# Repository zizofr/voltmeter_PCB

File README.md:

# ⚡ Digital Voltmeter (Custom PCB & Hardware Design)

A compact digital voltmeter designed around a custom Printed Circuit Board (PCB) created in KiCad. This repository contains the complete hardware design files, schematics, Gerber manufacturing outputs, and board renders prior to final firmware integration.

---

## 🖼️ Hardware & PCB Gallery

### Board Renders & Views
| Top View | Bottom View |
| :---: | :---: |
|  |  |

| Perspective View 1 | Perspective View 2 |
| :---: | :---: |
|  |  |

---

## 🛠️ Project Specifications & Features

- **EDA Tool:** KiCad
- **Board Architecture:** Custom 2-layer PCB
- **Hardware Features:**
  - Dedicated analog front-end voltage divider circuit for signal attenuation.
  - Onboard microcontroller interface for ADC sampling and processing.
  - Display interface output.
  - Optimized trace routing with solid ground plane shielding.
- **Manufacturing Package:** Full Gerber layer generation (F_Cu, B_Cu, Solder Masks, Silkscreens, and Drill files).

---

## 📂 Repository Structure

```text
├── gerber/              # Production Gerber and drill files (.gbr, .drl)
├── view_1.png              # High-resolution 3D renders (top, bottom, view_1, view_2)
├──view_2.png
├──top.png
├──bottom.png
├──firmware.ino  # ATmega328P C++ source code
├── voltmeter.kicad_pcb  # KiCad PCB board layout source file
├── voltmeter.kicad_sch  # KiCad schematic design source file
└── README.md            # Project documentation

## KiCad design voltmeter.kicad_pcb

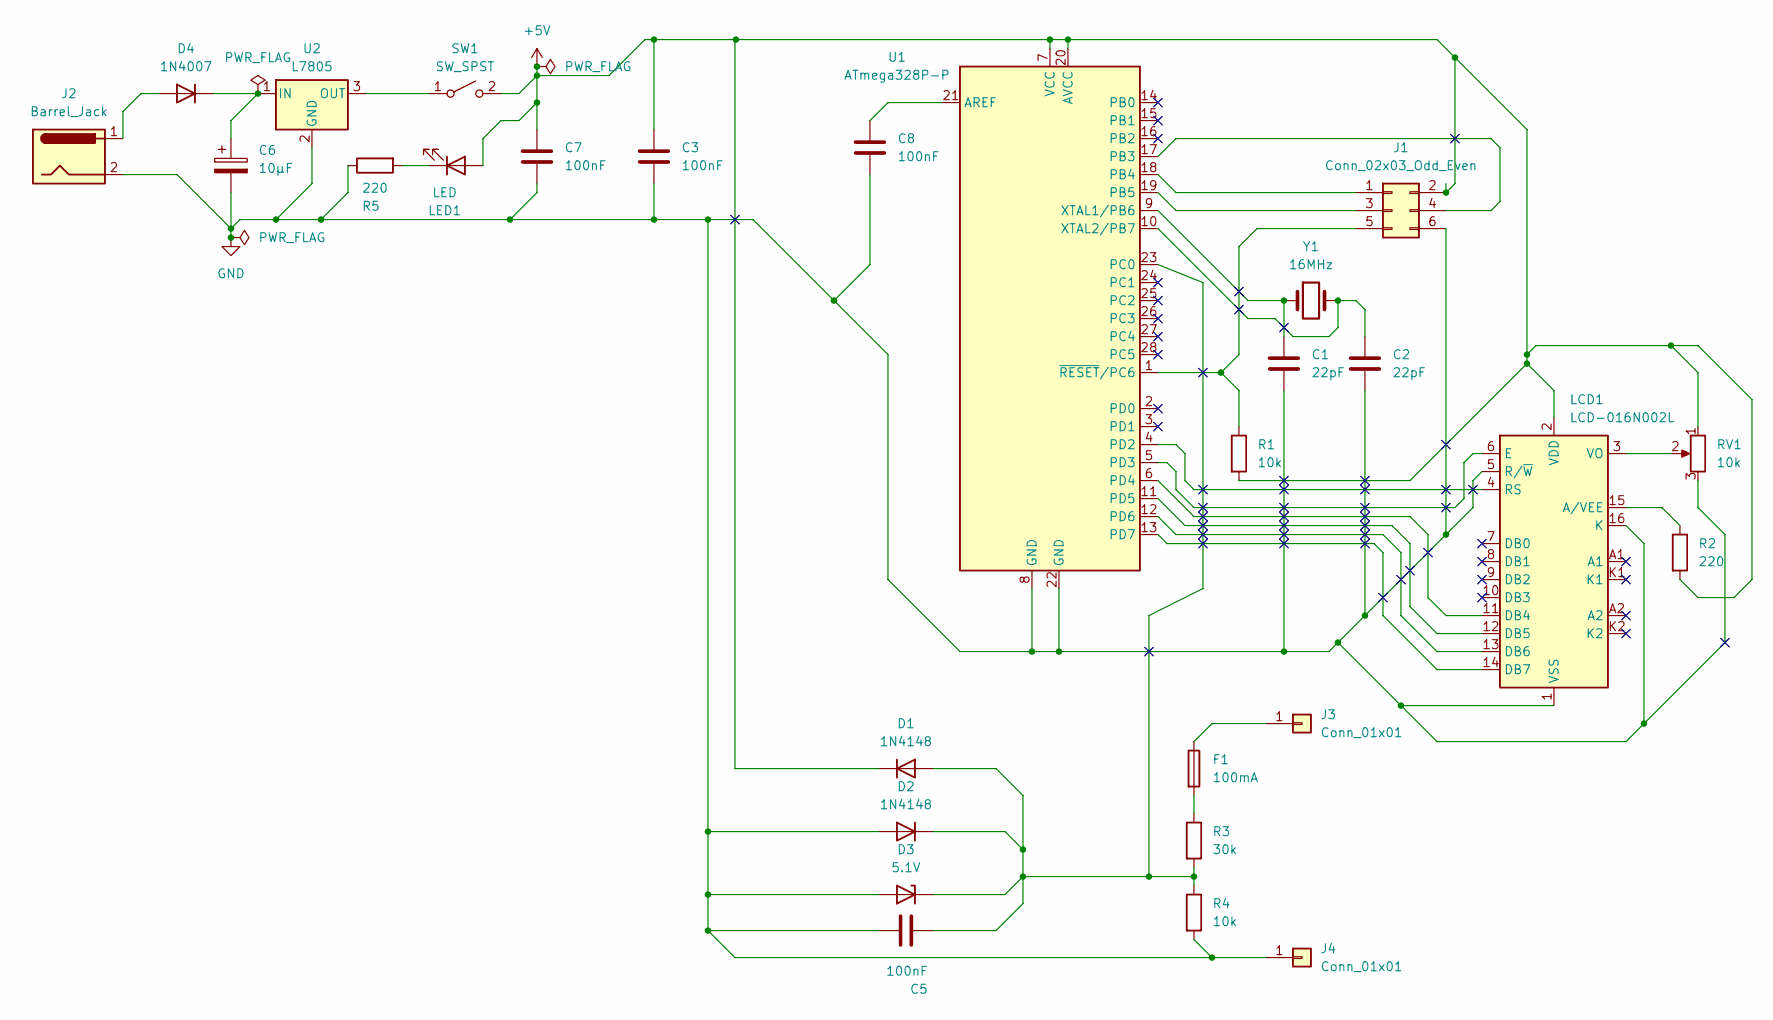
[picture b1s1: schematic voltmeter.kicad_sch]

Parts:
C1, C2: 22pF; C_Disc_D5.0mm_W2.5mm_P5.00mm
C3, C5, C7, C8: 100nF; C_Disc_D5.0mm_W2.5mm_P5.00mm
C6: 10µF; CP_Radial_D5.0mm_P2.00mm
D1, D2: 1N4148; D_DO-35_SOD27_P7.62mm_Horizontal
D3: 5.1V; D_DO-35_SOD27_P7.62mm_Horizontal
D4: 1N4007; D_DO-41_SOD81_P10.16mm_Horizontal
F1: 100mA; Fuse_1206_3216Metric
J1: Conn_02x03_Odd_Even; PinHeader_2x03_P2.54mm_Vertical
J2: Barrel_Jack; BarrelJack_Horizontal
J3, J4: Conn_01x01; Banana_Jack_1Pin
LCD1: LCD-016N002L; PinHeader_1x16_P2.54mm_Vertical
LED1: LED; LED_D5.0mm
R1, R4: 10k; R_Axial_DIN0207_L6.3mm_D2.5mm_P10.16mm_Horizontal
R2, R5: 220; R_Axial_DIN0207_L6.3mm_D2.5mm_P10.16mm_Horizontal
R3: 30k; R_Axial_DIN0207_L6.3mm_D2.5mm_P10.16mm_Horizontal
RV1: 10k; Potentiometer_Bourns_3386P_Vertical
SW1: SW_SPST; SW_SPST_Omron_B3F-40xx
U1: ATmega328P-P; DIP-28_W7.62mm
U2: L7805; TO-220-3_Vertical
Y1: 16MHz; Crystal_HC49-4H_Vertical

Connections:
+5V: C3.1, C7.1, D1.1 (K), J1.2, LCD1.2 (VDD), LED1.2 (A), R1.2, R2.2, RV1.1, SW1.2 (B), U1.7 (VCC), U1.20 (AVCC)
GND: C1.2, C2.2, C3.2, C5.2, C6.2, C7.2, C8.2, D2.2 (A), D3.2 (A), J1.6, J2.2, J4.1 (Pin_1_1), LCD1.1 (VSS), LCD1.5 (R/~W), LCD1.16 (K), R4.2, R5.1, RV1.3, U1.8 (GND), U1.22 (GND), U2.2 (GND)
unnamed: C5.1, D1.2 (A), D2.1 (K), D3.1 (K), R3.2, R4.1, U1.23 (PC0)
unnamed: D4.2 (A), J2.1
unnamed: C6.1, D4.1 (K), U2.1 (IN)
unnamed: F1.2, R3.1
unnamed: J1.1, U1.18 (PB4)
unnamed: J1.3, U1.19 (PB5)
unnamed: J1.4, U1.17 (PB3)
unnamed: J1.5, R1.1, U1.1 (~RESET/PC6)
unnamed: F1.1, J3.1 (Pin_1_1)
unnamed: LCD1.15 (A/VEE), R2.1
unnamed: LCD1.11 (DB4), U1.6 (PD4)
unnamed: LCD1.12 (DB5), U1.11 (PD5)
unnamed: LCD1.13 (DB6), U1.12 (PD6)
unnamed: LCD1.14 (DB7), U1.13 (PD7)
unnamed: LCD1.6 (E), U1.5 (PD3)
unnamed: LCD1.4 (RS), U1.4 (PD2)
unnamed: LCD1.3 (VO), RV1.2
unnamed: LED1.1 (K), R5.2
unnamed: SW1.1 (A), U2.3 (OUT)
unnamed: C8.1, U1.21 (AREF)
unnamed: C1.1, U1.9 (XTAL1/PB6), Y1.1
unnamed: C2.1, U1.10 (XTAL2/PB7), Y1.2

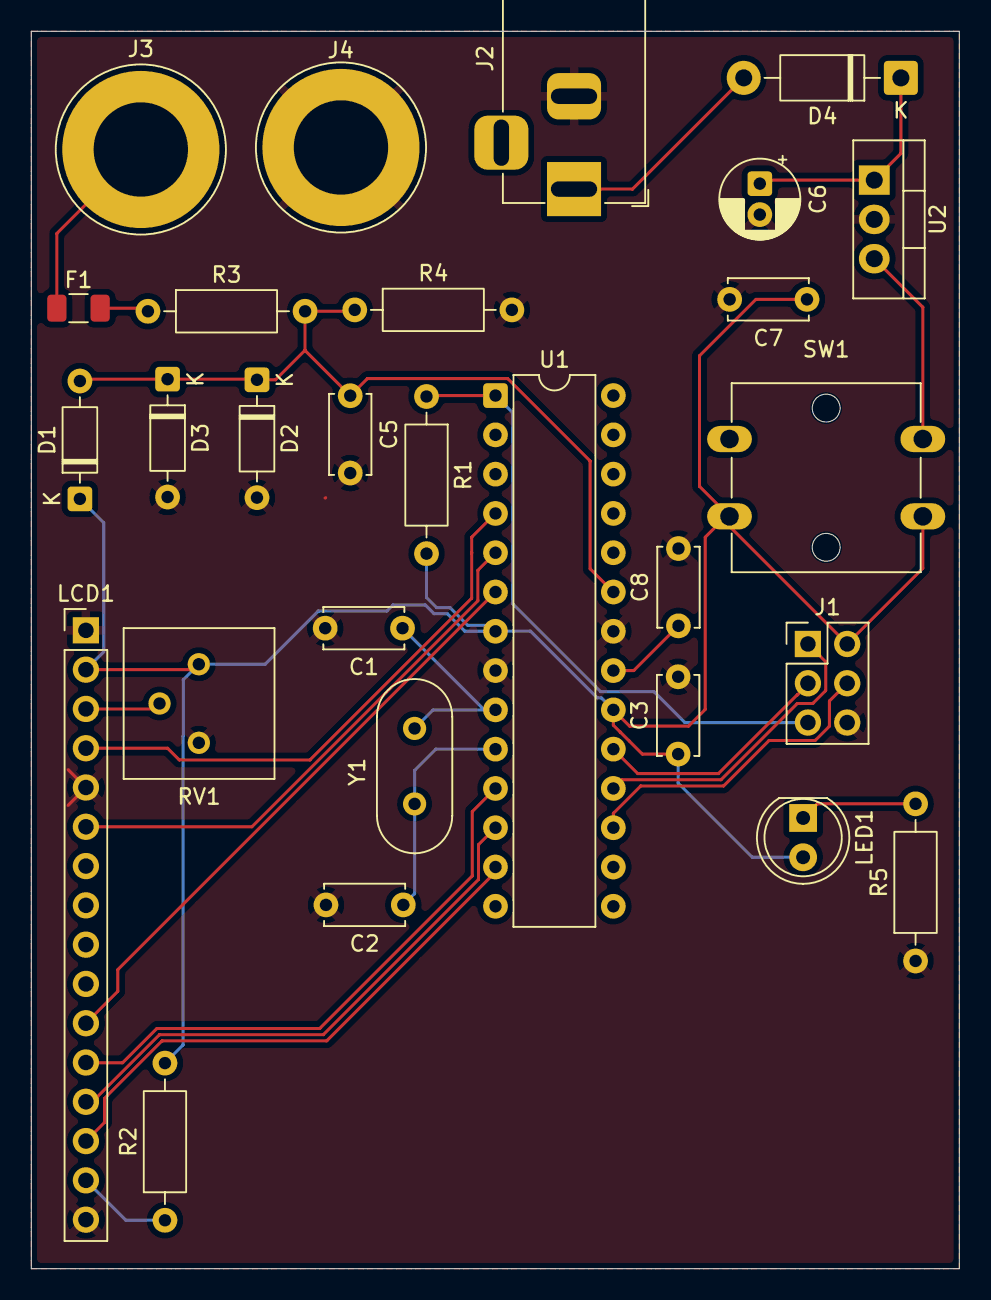
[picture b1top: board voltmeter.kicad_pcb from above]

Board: 2 copper layers, 60.0 x 80.0 mm, 28 parts (0 on the bottom side), 24 nets.

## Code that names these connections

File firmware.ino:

/*
  ============================================
  Digital Voltmeter - Official Firmware v1.0
  ============================================

  Target chip: ATmega328P-P (bare chip, 16MHz external crystal,
  programmed via ISP through J1)

  Function: Reads a 0-20V DC input through a resistor divider
  on ADC0, and displays the measured voltage on a 16x2 LCD.

  --------------------------------------------
  HARDWARE PIN MAPPING (matches the schematic)
  --------------------------------------------
  ATmega pin | Arduino name | Function
  -----------|--------------|------------------
  Pin 4      | D2 (PD2)     | LCD RS
  Pin 5      | D3 (PD3)     | LCD E
  Pin 6      | D4 (PD4)     | LCD DB4
  Pin 11     | D5 (PD5)     | LCD DB5
  Pin 12     | D6 (PD6)     | LCD DB6
  Pin 13     | D7 (PD7)     | LCD DB7
  Pin 23     | A0 (PC0)     | ADC input (from R3/R4 divider)

  --------------------------------------------
  VOLTAGE DIVIDER
  --------------------------------------------
  R3 = 30k (top, from probe input)
  R4 = 10k (bottom, to GND)
  Scales 0-20V input down to 0-5V at the ADC pin.
  Ratio to undo in software = (R3+R4)/R4 = 4.0

  --------------------------------------------
  BEFORE FIRST REAL USE
  --------------------------------------------
  1. Burn the bootloader onto U1 via J1 (if not already done),
     using an Arduino-as-ISP or USBasp programmer, board setting
     "Arduino Uno" (same chip/fuses/16MHz crystal).
  2. Upload this sketch through the same ISP connection.
  3. Calibrate: apply a known, accurate voltage (measured with a
     trusted multimeter) to the probes, and adjust
     CALIBRATION_FACTOR below until the LCD matches that reading.
     Re-upload after changing it.
*/

#include <LiquidCrystal.h>

// ---------------- Pin setup ----------------
const int PIN_RS = 2;
const int PIN_EN = 3;
const int PIN_D4 = 4;
const int PIN_D5 = 5;
const int PIN_D6 = 6;
const int PIN_D7 = 7;

LiquidCrystal lcd(PIN_RS, PIN_EN, PIN_D4, PIN_D5, PIN_D6, PIN_D7);

const int ADC_PIN = A0;

// ---------------- Circuit constants ----------------
const float VREF = 5.0;             // ADC reference voltage (AVCC/AREF)
const int   ADC_MAX = 1023;         // 10-bit ADC resolution
const float DIVIDER_RATIO = 4.0;    // (R3 + R4) / R4 = (30k + 10k) / 10k

// ---------------- Calibration ----------------
// Set this after testing against a known-accurate voltage source.
// Formula: CALIBRATION_FACTOR = actual / displayed
float CALIBRATION_FACTOR = 1.0;

// ---------------- Sampling ----------------
const int   NUM_SAMPLES     = 30;   // averaged per reading, reduces noise/jitter
const int   SAMPLE_DELAY_MS = 2;    // small delay between samples
const int   UPDATE_DELAY_MS = 250;  // how often the display refreshes

// ---------------- Safety display ----------------
const float OVER_RANGE_VOLTS = 20.5; // slightly above rated 20V max

void setup() {
  lcd.begin(16, 2);
  lcd.clear();
  lcd.setCursor(0, 0);
  lcd.print("Digital");
  lcd.setCursor(0, 1);
  lcd.print("Voltmeter v1.0");
  delay(1500);
  lcd.clear();
}

void loop() {
  float vIn = readVoltage();

  lcd.setCursor(0, 0);
  lcd.print("Voltage:");

  lcd.setCursor(0, 1);
  if (vIn > OVER_RANGE_VOLTS) {
    lcd.print("OVER RANGE!   ");
  } else {
    lcd.print(vIn, 2);
    lcd.print(" V");
    lcd.print("      "); // clears leftover digits from a previous longer reading
  }

  delay(UPDATE_DELAY_MS);
}

// Reads and averages the ADC, then converts to the real input voltage
float readVoltage() {
  long sum = 0;
  for (int i = 0; i < NUM_SAMPLES; i++) {
    sum += analogRead(ADC_PIN);
    delay(SAMPLE_DELAY_MS);
  }
  float rawAverage = sum / (float)NUM_SAMPLES;

  float vAtPin = (rawAverage / (float)ADC_MAX) * VREF;
  float vIn = vAtPin * DIVIDER_RATIO * CALIBRATION_FACTOR;

  return vIn;
}
